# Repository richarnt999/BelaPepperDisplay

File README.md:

BelaPepperDisplay
=================

My first github project...

A 1U 18hp eurorack module for interfacing over I2C with Bela Pepper. It contains a 0.91" SSD1306 OLED, two rotary encoders, and is run by an arduino nano every. I plan to use it to control parameters on the Bela via a menu structure.

240428 status: communication between arduino, rotary encoder and oled is established. Circuit rev1 designed. Next step is to establish I2C with the Bela.

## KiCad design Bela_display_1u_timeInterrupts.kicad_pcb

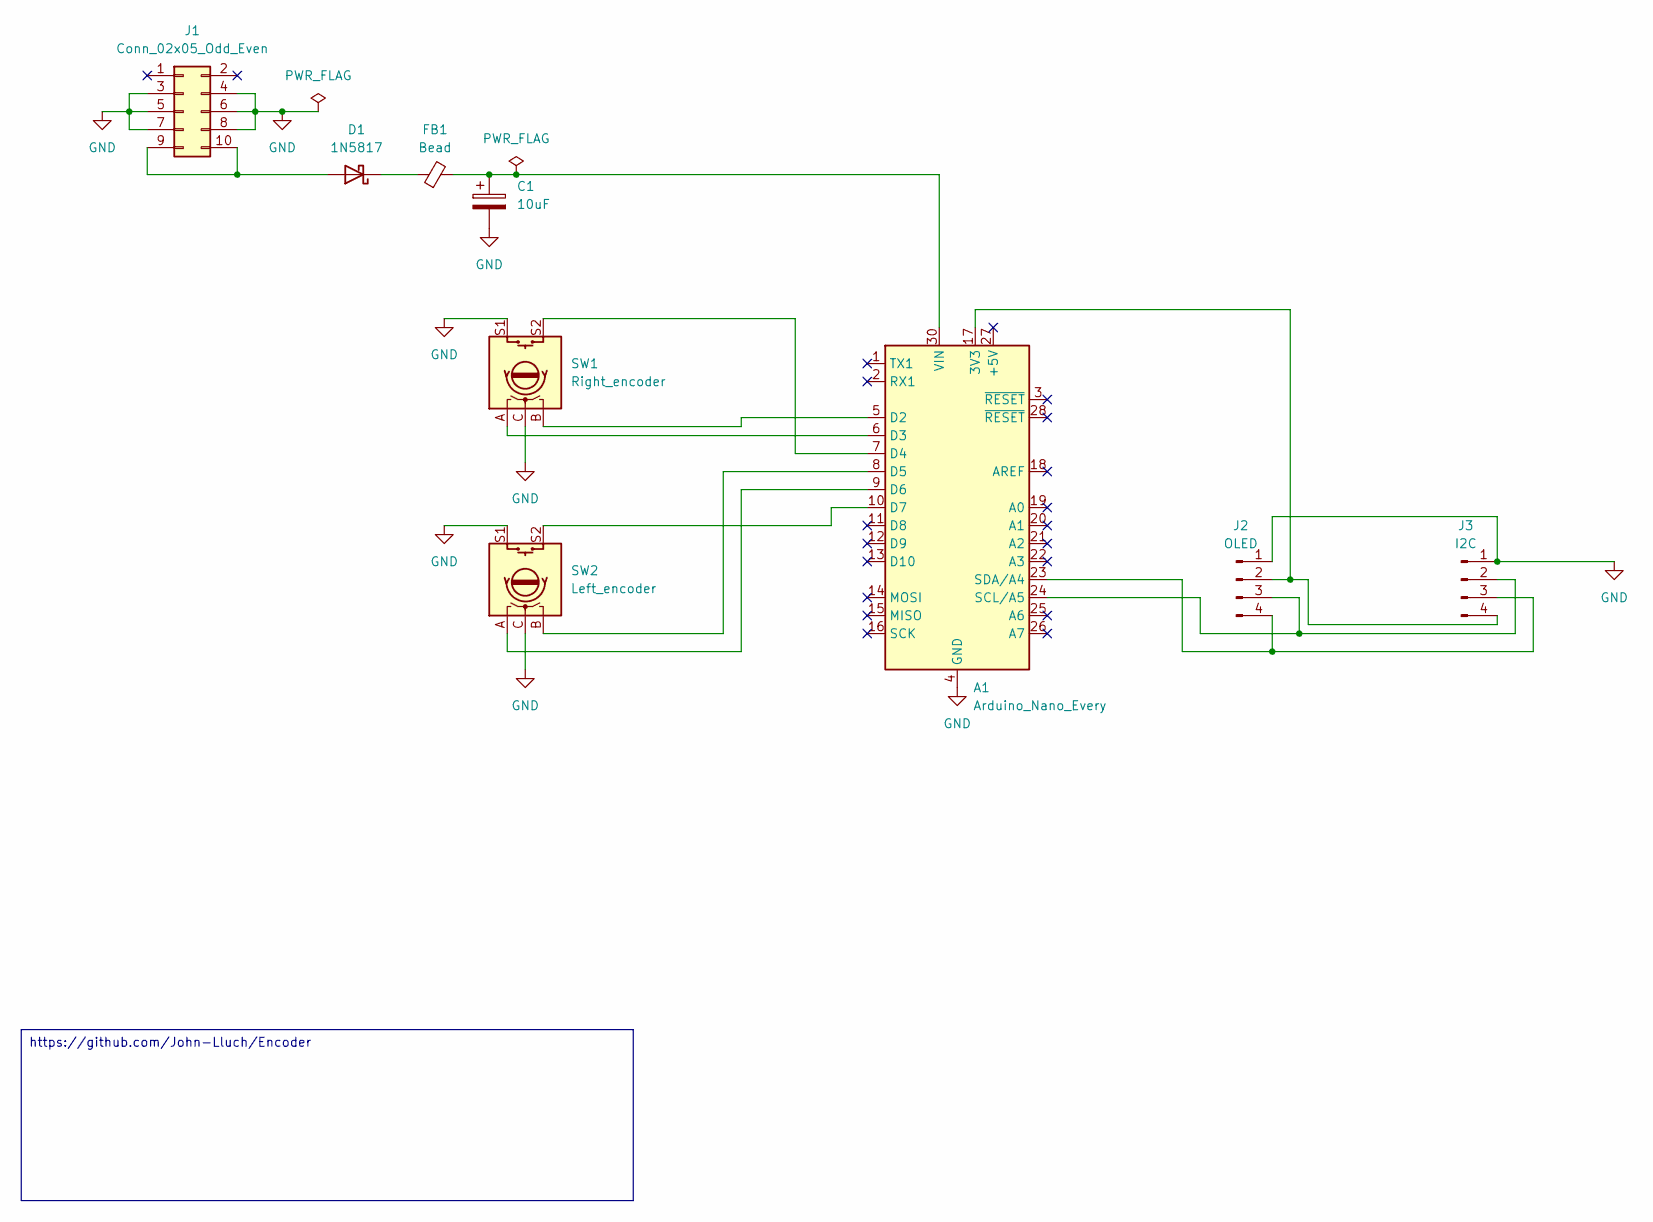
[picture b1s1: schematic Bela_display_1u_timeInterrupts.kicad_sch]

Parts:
A1: Arduino_Nano_Every; Arduino_Nano
C1: 10uF; CP_Radial_D8.0mm_P2.50mm
D1: 1N5817; D_DO-41_SOD81_P10.16mm_Horizontal
FB1: Bead; R_Axial_DIN0207_L6.3mm_D2.5mm_P7.62mm_Horizontal
J1: Conn_02x05_Odd_Even; IDC-Header_2x05_P2.54mm_Vertical
J2: OLED; SSD1306-0.91-OLED-4pin-128x32
J3: I2C; PinHeader_1x04_P2.54mm_Vertical
SW1: Right_encoder; RotaryEncoder_Alps_EC11E-Switch_Vertical_H20mm
SW2: Left_encoder; RotaryEncoder_Alps_EC11E-Switch_Vertical_H20mm

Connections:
GND: A1.4 (GND), A1.29 (GND), C1.2, J1.3, J1.4, J1.5, J1.6, J1.7, J1.8, J2.1, J3.1, SW1.C, SW1.S1, SW2.C, SW2.S1
unnamed: A1.17 (3V3), J2.2, J3.4
unnamed: A1.5 (D2), SW1.B
unnamed: A1.6 (D3), SW1.A
unnamed: A1.7 (D4), SW1.S2
unnamed: A1.8 (D5), SW2.B
unnamed: A1.9 (D6), SW2.A
unnamed: A1.10 (D7), SW2.S2
unnamed: A1.24 (SCL/A5), J2.3, J3.2
unnamed: A1.23 (SDA/A4), J2.4, J3.3
unnamed: A1.30 (VIN), C1.1, FB1.2
unnamed: D1.2 (A), J1.9, J1.10
unnamed: D1.1 (K), FB1.1

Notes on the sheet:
https://github.com/John-Lluch/Encoder

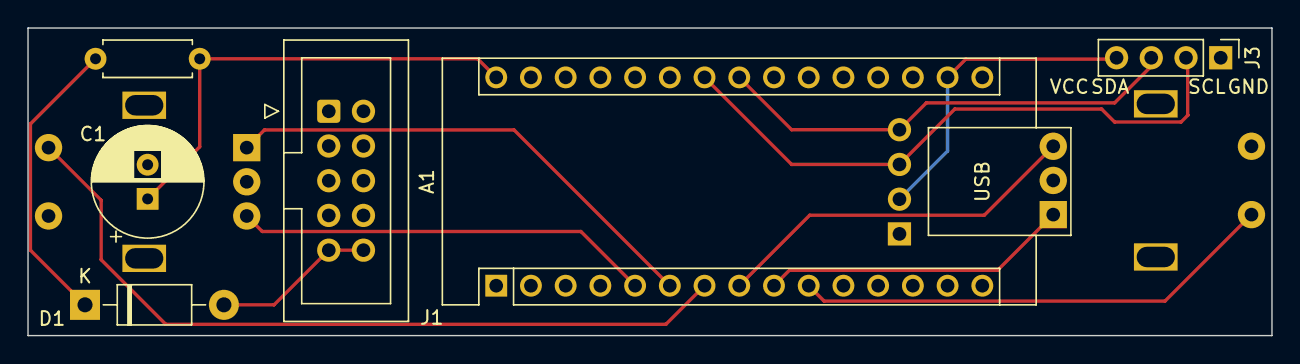
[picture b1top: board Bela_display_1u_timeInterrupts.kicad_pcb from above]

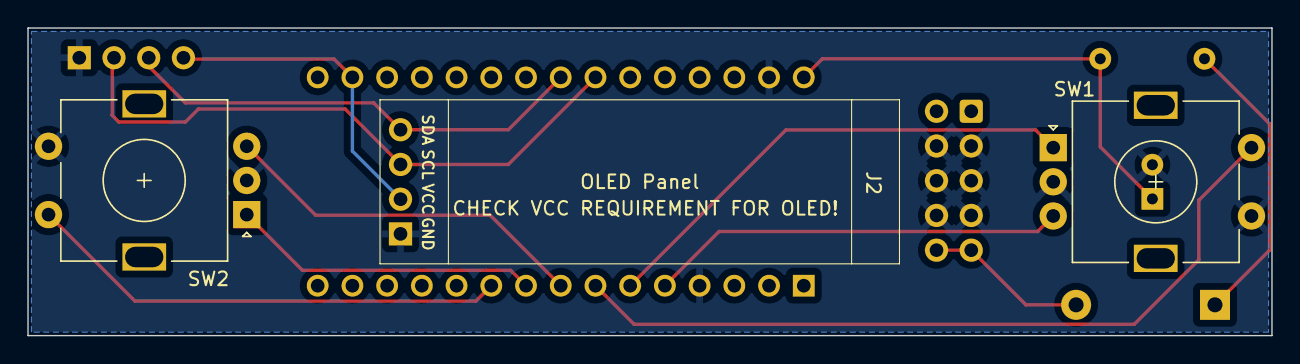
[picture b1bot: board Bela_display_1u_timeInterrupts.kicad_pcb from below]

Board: 2 copper layers, 91.0 x 22.5 mm, 9 parts (3 on the bottom side), 13 nets.

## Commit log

2024-04-28 Created README.md
2024-04-28 Initial commit
    Kicad schematic, board layout. Arduino sketch with communication to single encoder and oled.
